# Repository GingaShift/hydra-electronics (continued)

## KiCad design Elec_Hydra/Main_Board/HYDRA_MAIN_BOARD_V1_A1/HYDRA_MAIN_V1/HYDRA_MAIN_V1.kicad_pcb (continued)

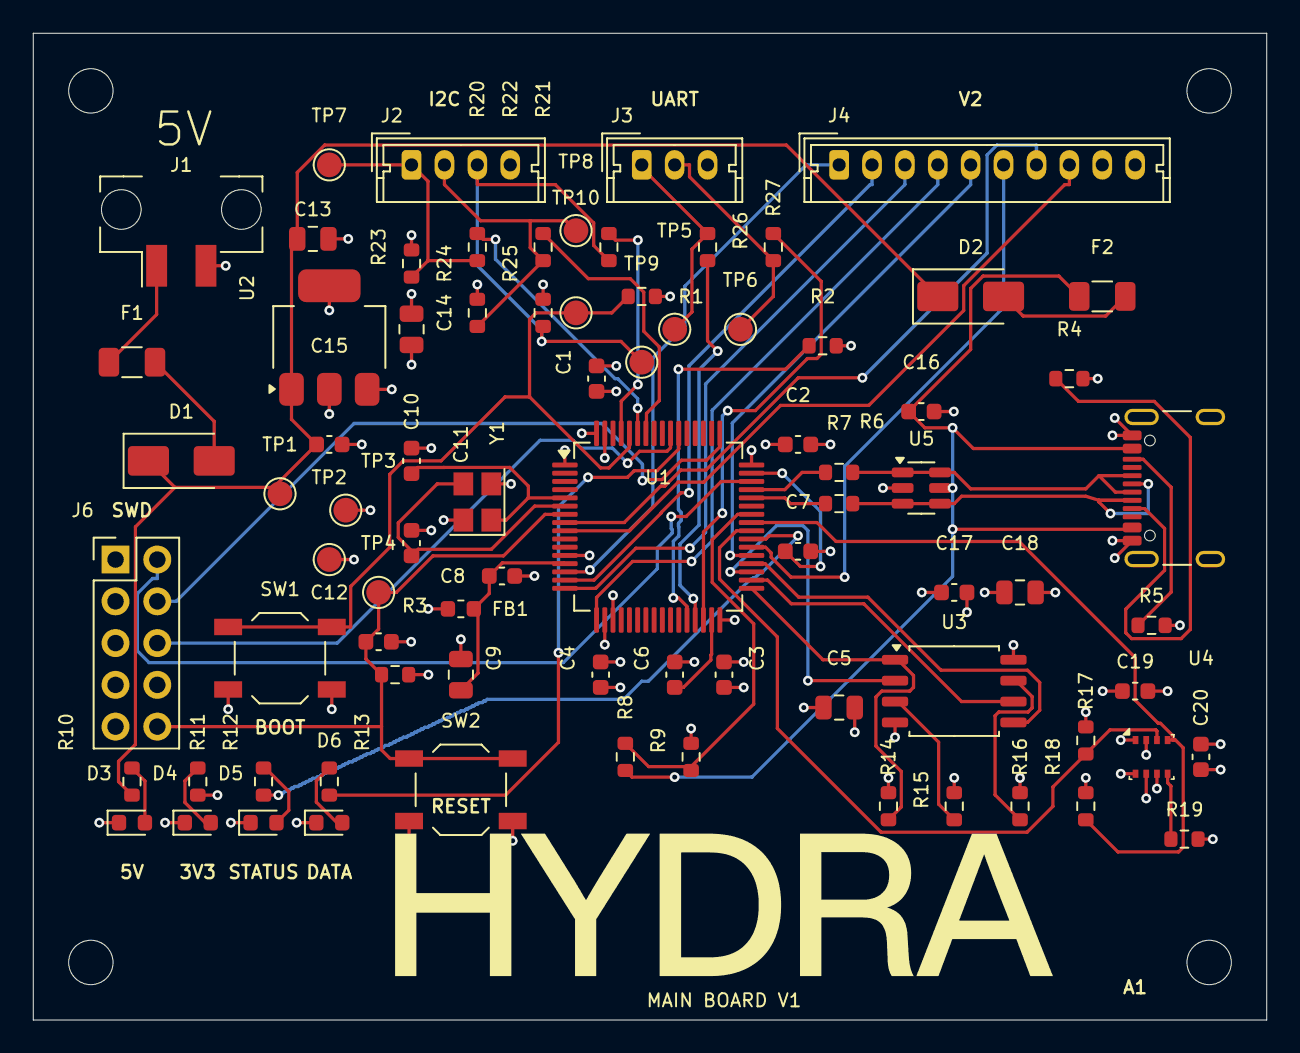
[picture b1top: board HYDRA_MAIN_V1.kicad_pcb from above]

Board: 4 copper layers, 75.0 x 60.0 mm, 85 parts (0 on the bottom side), 58 nets.

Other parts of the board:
LOGO1: HYDRA_Official_Wordmark_40mm
U2: AP7361C-33E-13; SOT-223-3_TabPin2

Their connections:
+3V3: U2.3; also elsewhere on the board
+5V_SYS: U2.1; also elsewhere on the board
GND: U2.2; also elsewhere on the board

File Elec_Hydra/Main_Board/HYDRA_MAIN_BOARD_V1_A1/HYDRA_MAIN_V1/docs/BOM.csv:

Designators,Quantity,Value,Manufacturer,MPN,Footprint,Notes
U1,1,STM32F405RGT6,STMicroelectronics,STM32F405RGT6,HYDRA:LQFP-64_10x10mm_P0.5mm,
"C1,C2,C3,C4,C8,C12,C15,C16,C17,C19,C20",11,100n,Murata,GRM188R71C104KA01D,HYDRA:C_0603_1608Metric,
"C5,C9,C13,C14,C18",5,4.7u,Murata,GRM21BR71A475KA73L,HYDRA:C_0805_2012Metric,
"C6,C7",2,2.2u,Murata,GRM188R71A225KE15D,HYDRA:C_0603_1608Metric,
FB1,1,600R@100MHz,Murata,BLM18AG601SN1D,HYDRA:L_0603_1608Metric,
Y1,1,8MHz CL10pF,ECS,ECS-80-10-33-CHN-TR,HYDRA:Crystal_SMD_3225-4Pin_3.2x2.5mm,"CL10pF; C0max5pF ESRmax400R; gmcrit0.91mA/V, qualifier oscillation"
"C10,C11",2,14p,Murata,GRM1885C1H140JA01D,HYDRA:C_0603_1608Metric,
"R1,R2,R3,R14,R15,R16,R19,R25",8,10k,Yageo,RC0603FR-0710KL,HYDRA:R_0603_1608Metric,
SW1,1,BOOT,E-Switch,TL3342F160QG,HYDRA:SW_SPST_TL3342,
SW2,1,RESET,E-Switch,TL3342F160QG,HYDRA:SW_SPST_TL3342,
J1,1,5V POWER IN,Molex,43650-0221,HYDRA:Molex_Micro-Fit_3.0_43650-0221_1x02_P3.00mm_Vertical,
"F1,F2",2,0.50A hold,Littelfuse,1206L050/15YR,HYDRA:Fuse_1206_3216Metric,
"D1,D2",2,SS14,Vishay,SS14-E3/61T,HYDRA:D_SMA,OR passif; protege retours et inversion polarite
U2,1,AP7361C-33E-13,Diodes Inc.,AP7361C-33E-13,HYDRA:SOT-223-3_TabPin2,"SOT223: 1IN 2GND/tab 3OUT, pas AMS1117"
J5,1,USB-C USB2 DEVICE,GCT,USB4105-GF-A,HYDRA:USB_C_Receptacle_GCT_USB4105-xx-A_16P_TopMnt_Horizontal,
"R4,R5",2,5.1k,Yageo,RC0603FR-075K1L,HYDRA:R_0603_1608Metric,
U5,1,USBLC6-2SC6,STMicroelectronics,USBLC6-2SC6,HYDRA:SOT-23-6,
"R6,R7",2,22,Yageo,RC0603FR-0722RL,HYDRA:R_0603_1608Metric,
R8,1,33k,Yageo,RC0603FR-0733KL,HYDRA:R_0603_1608Metric,
R9,1,82k,Yageo,RC0603FR-0782KL,HYDRA:R_0603_1608Metric,
R10,1,3.3k,Yageo,RC0603FR-073K3L,HYDRA:R_0603_1608Metric,
D3,1,PWR_5V,Lite-On,LTST-C190KGKT,HYDRA:LED_0603_1608Metric,green
"R11,R13,R23,R24",4,2.2k,Yageo,RC0603FR-072K2L,HYDRA:R_0603_1608Metric,
D4,1,PWR_3V3,Lite-On,LTST-C190KGKT,HYDRA:LED_0603_1608Metric,green
"R12,R22,R26,R27",4,1k,Yageo,RC0603FR-071KL,HYDRA:R_0603_1608Metric,
D5,1,STATUS,Lite-On,LTST-C190TBKT,HYDRA:LED_0603_1608Metric,blue
D6,1,DATA,Lite-On,LTST-C190KSKT,HYDRA:LED_0603_1608Metric,yellow
U3,1,W25Q128JVSIQ,Winbond,W25Q128JVSIQ,HYDRA:SOIC-8_5.23x5.23mm_P1.27mm,
U4,1,BME280,Bosch Sensortec,BME280,HYDRA:Bosch_LGA-8_2.5x2.5mm_P0.65mm_ClockwisePinNumbering,"I2C3 adresse7bits0x77, CSB1 SDO1"
"R17,R18",2,4.7k,Yageo,RC0603FR-074K7L,HYDRA:R_0603_1608Metric,
J2,1,POWER I2C ALERT,Molex,53253-0470,HYDRA:Molex_Micro-Latch_53253-0470_1x04_P2.00mm_Vertical,
"R20,R21",2,47,Yageo,RC0603FR-0747RL,HYDRA:R_0603_1608Metric,
J3,1,RPi UART 3V3,Molex,53253-0370,HYDRA:Molex_Micro-Latch_53253-0370_1x03_P2.00mm_Vertical,"vers Navigator SERIAL3: 1 vers RX3, 2 vers TX2, 3 vers GND6"
J4,1,8 GPIO V2 LOGIC,Molex,53253-1070,HYDRA:Molex_Micro-Latch_53253-1070_1x10_P2.00mm_Vertical,3V3 logique max50mA; aucune puissance actionneur
J6,1,SWD 2.54mm,Wurth,61301021121,HYDRA:PinHeader_2x05_P2.54mm_Vertical,Standard ARM signaux mais pas pas1.27: adaptateur requis

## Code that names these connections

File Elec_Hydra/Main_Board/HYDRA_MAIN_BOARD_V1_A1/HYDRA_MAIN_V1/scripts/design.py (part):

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C('2.2u','VCAP1',(0,195,72),(37,35,0));C('2.2u','VCAP2',(0,220,72),(47,43,90))
add('FB1','Device:FerriteBead','600R@100MHz','Inductor_SMD:L_0603_1608Metric',{1:'+3V3',2:'VDDA'},(0,170,100),(35,24,0),'BLM18AG601SN1D','Murata')
C('100n','VDDA',(0,195,100),(35,28,0));C('4.7u','VDDA',(0,220,100),(31,26,90),'Capacitor_SMD:C_0805_2012Metric')
add('Y1','Device:Crystal_GND24','8MHz CL10pF','Crystal:Crystal_SMD_3225-4Pin_3.2x2.5mm',{1:'HSE_IN',2:'GND',3:'HSE_OUT',4:'GND'},(0,180,135),(33,34,90),'ECS-80-10-33-CHN-TR','ECS','CL10pF; C0max5pF ESRmax400R; gmcrit0.91mA/V, qualifier oscillation')
C('14p','HSE_IN',(0,210,135),(30,32,90));C('14p','HSE_OUT',(0,235,135),(30,36,90))
R('10k','BOOT0','GND',(0,170,165),(37,21,0));R('10k','BOOT1','GND',(0,195,165),(51,23,0));R('10k','NRST','+3V3',(0,220,165),(29,44,0));C('100n','NRST',(0,245,165),(29,48,0))
for ref,net,xy,sx in [('SW1','BOOT0',(19,52,0),180),('SW2','NRST',(30,52,0),230)]:
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R('22','USB_DM_EXT','USB_DM',(1,200,158),(36,48,90));R('22','USB_DP_EXT','USB_DP',(1,230,158),(39,48,90))
R('33k','VBUS_USB','VBUS_SENSE',(1,200,190),(43,49,90));R('82k','VBUS_SENSE','GND',(1,230,190),(47,49,90))
# Four LEDs only status/data connected GPIO; rest supply indicators.
for i,(net,label,color,mpn,res,xy) in enumerate([('+5V_SYS','PWR_5V','green','LTST-C190KGKT','3.3k',(7,61,0)),('+3V3','PWR_3V3','green','LTST-C190KGKT','2.2k',(12,61,0)),('LED_STATUS','STATUS','blue','LTST-C190TBKT','1k',(17,61,0)),('LED_DATA','DATA','yellow','LTST-C190KSKT','2.2k',(22,61,0))]):
 ref='D'+str(i+3);ln='LED_A'+str(i)
 R(res,net,ln,(2,40+i*65,180),(xy[0],57,90))
 add(ref,'Device:LED',label,'LED_SMD:LED_0603_1608Metric',{1:'GND',2:ln},(2,40+i*65,205),xy,mpn,'Lite-On',color)
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add('U3','Memory_Flash:W25Q128JVS','W25Q128JVSIQ','Package_SO:SOIC-8_5.23x5.23mm_P1.27mm',{1:'FLASH_CS',2:'FLASH_MISO',3:'FLASH_WP',4:'GND',5:'FLASH_MOSI',6:'FLASH_SCK',7:'FLASH_HOLD',8:'+3V3'},(2,60,65),(63,34,0),'W25Q128JVSIQ','Winbond')
C('100n','+3V3',(2,100,40),(64,28,0));C('4.7u','+3V3',(2,125,40),(69,28,0),'Capacitor_SMD:C_0805_2012Metric')
for i,net in enumerate(['FLASH_CS','FLASH_WP','FLASH_HOLD']):R('10k',net,'+3V3',(2,35+i*40,105),(59+i*4,42,90))
add('U4','Sensor:BME280','BME280','Package_LGA:Bosch_LGA-8_2.5x2.5mm_P0.65mm_ClockwisePinNumbering',{1:'GND',2:'+3V3',3:'BME_SDA',4:'BME_SCL',5:'BME_ADDR',6:'+3V3',7:'GND',8:'+3V3'},(2,205,65),(77,48,0),'BME280','Bosch Sensortec','I2C3 adresse7bits0x77, CSB1 SDO1')
C('100n','+3V3',(2,245,35),(76,44,0));C('100n','+3V3',(2,245,65),(81,48,90))
R('4.7k','BME_SDA','+3V3',(2,185,105),(72,47,90));R('4.7k','BME_SCL','+3V3',(2,220,105),(72,51,90))
R('10k','BME_ADDR','+3V3',(2,250,105),(80,53,0))
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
